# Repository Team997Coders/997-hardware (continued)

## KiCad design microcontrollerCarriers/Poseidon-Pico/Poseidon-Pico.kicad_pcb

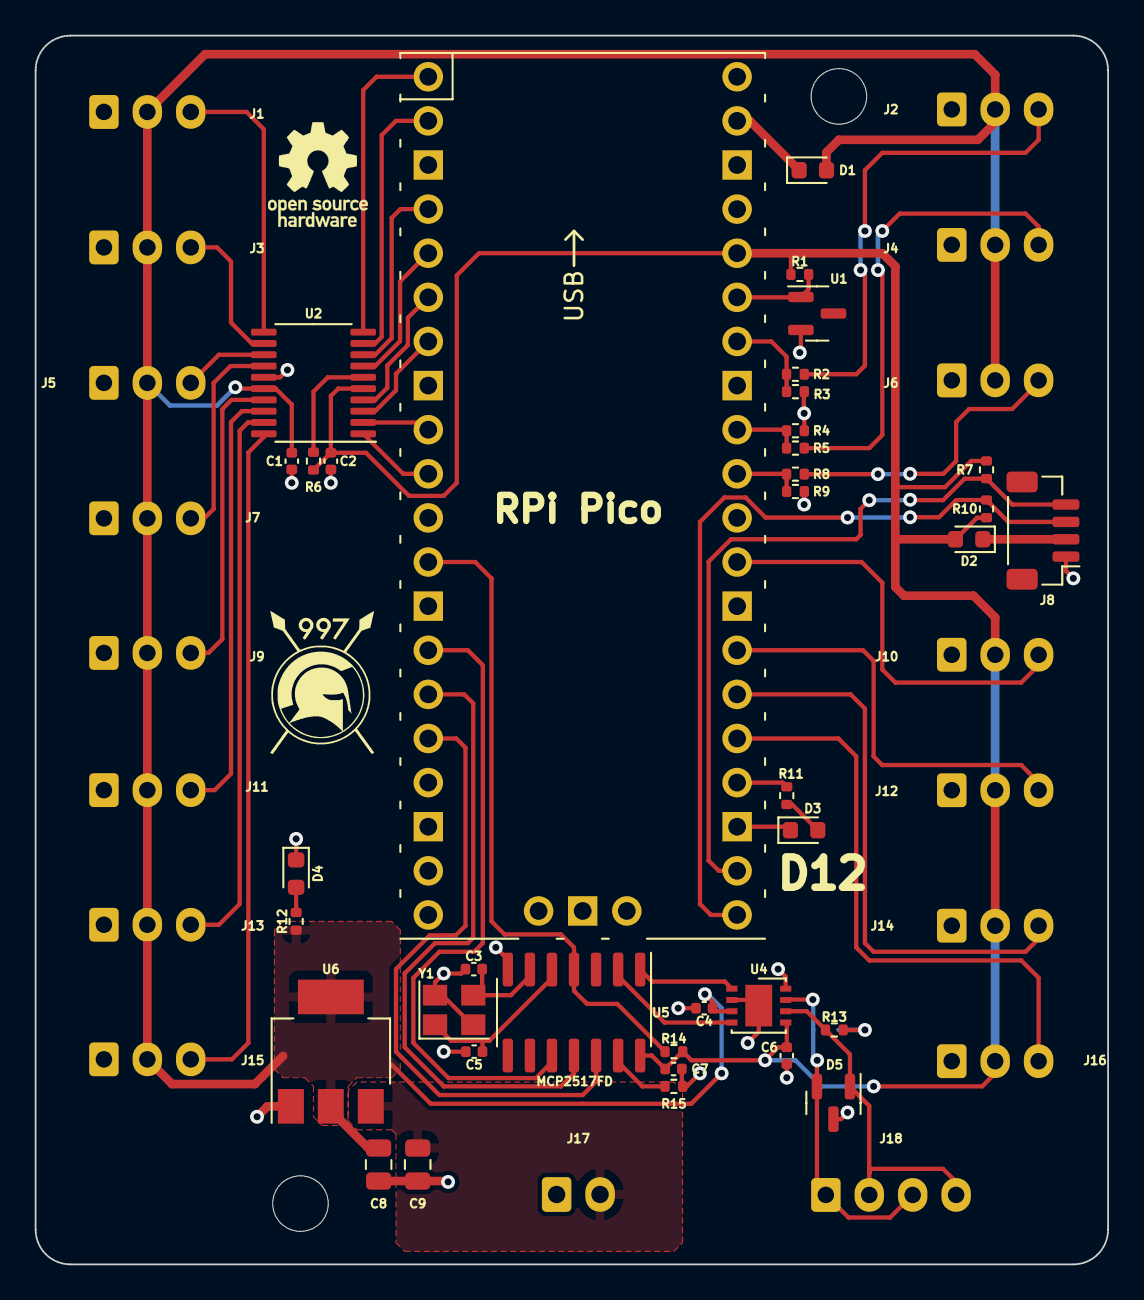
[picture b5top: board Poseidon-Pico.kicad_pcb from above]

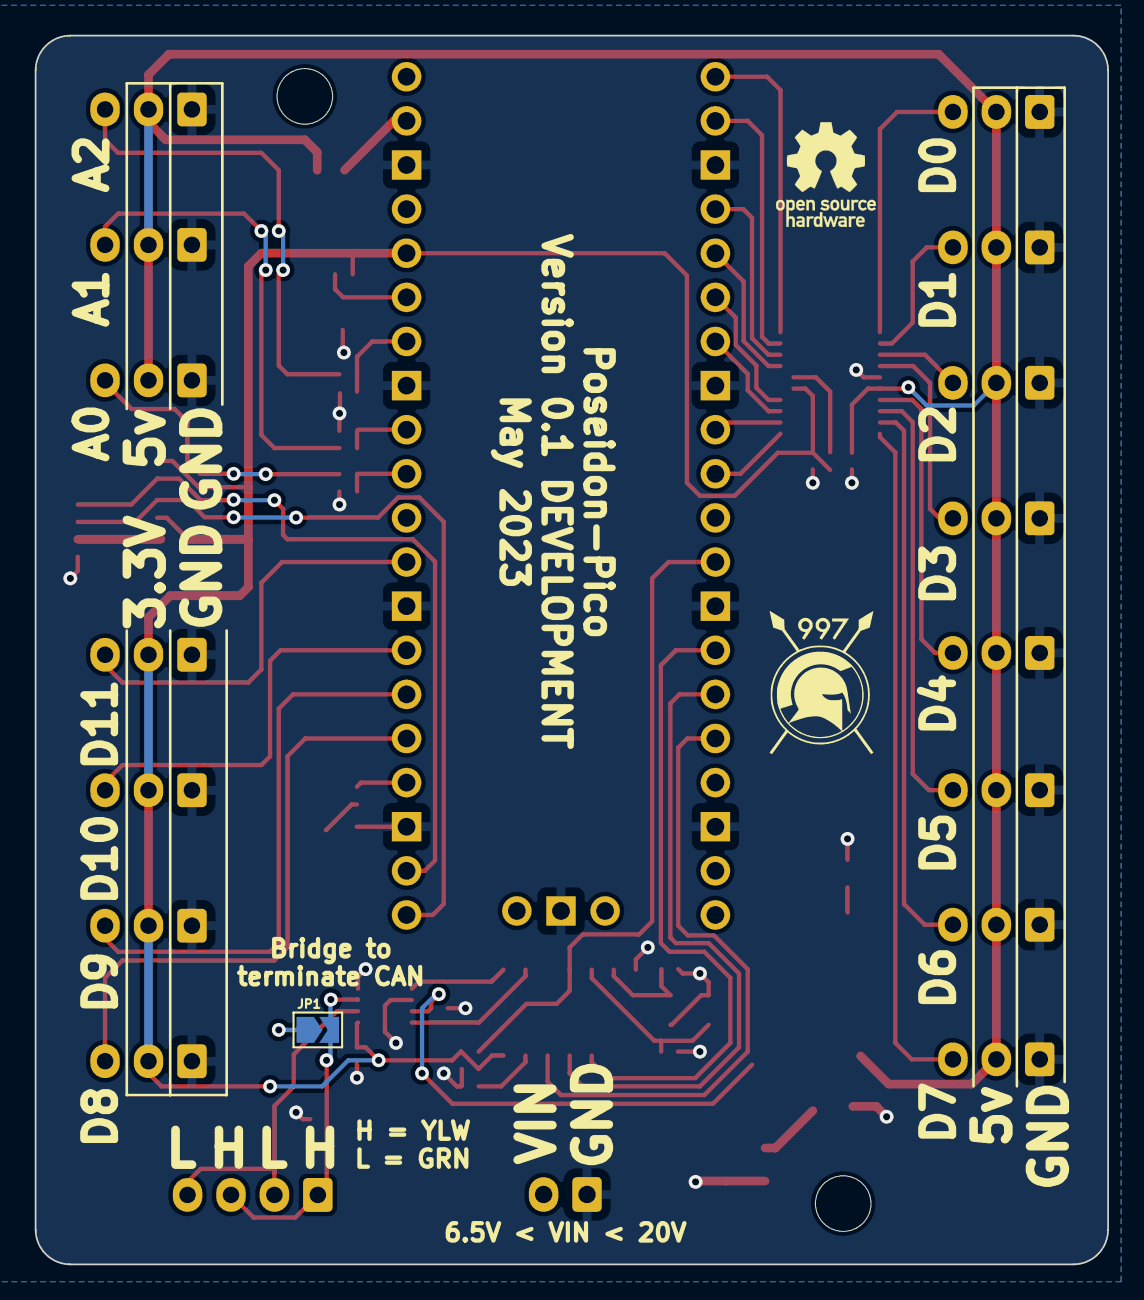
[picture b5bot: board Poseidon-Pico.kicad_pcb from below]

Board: 2 copper layers, 61.8 x 70.8 mm, 59 parts (3 on the bottom side), 51 nets.

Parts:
1, 2: LOGO; 997-big
C1, C2, C4, C6, C7: 0.1 uF; C_0402_1005Metric
C3, C5: 10 pF; C_0402_1005Metric
C8: 10 uF; C_0805_2012Metric
C9: 10 uF 35v; C_0805_2012Metric
D1, D2: D_Schottky; D_0603_1608Metric
D3, D4: LED; LED_0603_1608Metric
D5: NUP2105L; SOT-23
J1, J2, J3, J4, J5, J6, J7, J9, J10, J11, J12, J13, J14, J15, J16: Conn_01x03; JST_XH_B3B-XH-A_1x03_P2.50mm_Vertical
J8: Conn_01x04; JST_SH_BM04B-SRSS-TB_1x04-1MP_P1.00mm_Vertical
J17: Conn_01x02; JST_XH_B2B-XH-A_1x02_P2.50mm_Vertical
J18: Conn_01x04; JST_XH_B4B-XH-A_1x04_P2.50mm_Vertical
JP1: Jumper_2_Open; SolderJumper-2_P1.3mm_Open_TrianglePad1.0x1.5mm
R1, R6, R7, R10: 10k; R_0402_1005Metric
R2, R5, R8: 1.5k; R_0402_1005Metric
R3, R4, R9: 2.7k; R_0402_1005Metric
R11, R12: 300; R_0402_1005Metric
R13: 120; R_0402_1005Metric
R14, R15: 1k; R_0402_1005Metric
U1: LM4040DBZ-3; SOT-23
U2: TXB0108DQSR; TSSOP-20_4.4x6.5mm_P0.65mm
U3: Pico; RPi_Pico_SMD_TH
U4: MCP2542FDxMF; DFN-8-1EP_3x3mm_P0.65mm_EP1.55x2.4mm
U5: MCP2517FD-xSL; SOIC-14_3.9x8.7mm_P1.27mm
U6: NCP1117-5.0_SOT223; SOT-223-3_TabPin2
Y1: 40 MHz 9 pF; Crystal_SMD_3225-4Pin_3.2x2.5mm
oshw_b: OSHW-Logo_5.7x6mm_SilkScreen
oshw_f: OSHW-Logo_5.7x6mm_SilkScreen

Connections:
3ADC0: R8.2, R9.1, U3.31 (GPIO26_ADC0)
3ADC1: R4.1, R5.2, U3.32 (GPIO27_ADC1)
3ADC2: R2.2, R3.1, U3.34 (GPIO28_ADC2)
3GPIO0: U2.10 (A8), U3.1 (GPIO0)
3GPIO1: U2.9 (A7), U3.2 (GPIO1)
3GPIO2: U2.8 (A6), U3.4 (GPIO2)
3GPIO3: U2.7 (A5), U3.5 (GPIO3)
3GPIO4: U2.4 (A4), U3.6 (GPIO4)
3GPIO5: U2.3 (A3), U3.7 (GPIO5)
3GPIO6: U2.2 (A2), U3.9 (GPIO6)
3GPIO7: U2.1 (A1), U3.10 (GPIO7)
5ADC0: J6.3, R8.1
5ADC1: J4.3, R5.1
5ADC2: J2.3, R2.1
5GPIO0: J1.3, U2.11 (B8)
5GPIO1: J3.3, U2.12 (B7)
5GPIO2: J5.3, U2.13 (B6)
5GPIO3: J7.3, U2.14 (B5)
5GPIO4: J9.3, U2.17 (B4)
5GPIO5: J11.3, U2.18 (B3)
5GPIO6: J13.3, U2.19 (B2)
5GPIO7: J15.3, U2.20 (B1)
+3.3V: C2.1, C6.1, C7.1, D2.2 (A), J10.2, J12.2, J14.2, J16.2, R1.1, R6.1, R7.1, R10.1, R14.1, U2.5 (VCCA), U3.36 (3V3), U4.5 (VIO), U5.14 (VDD)
+5V: C1.1, C4.2, C8.1, D1.2 (A), J1.2, J2.2, J3.2, J4.2, J5.2, J6.2, J7.2, J9.2, J11.2, J13.2, J15.2, R12.2, U2.16 (VCCB), U4.3 (VDD), U6.2 (VO)
/CAN_CLK_A: C5.2, U5.5 (OSC2), Y1.1
/CAN_CLK_B: C3.1, U5.6 (OSC1), Y1.3
/RXCAN: U4.4 (RXD), U5.2 (RXCAN)
/TXCAN: U4.1 (TXD), U5.1 (TXCAN)
ADC_VREF: R1.2, U1.1 (K), U3.35 (ADC_VREF)
CANH: D5.2 (K), J18.1, J18.3, JP1.2 (B), U4.7 (CANH)
CANL: D5.1 (K), J18.2, J18.4, R13.2, U4.6 (CANL)
CAN_CS: R15.2, U5.13 (nCS)
CAN_INT: R14.2, U3.12 (GPIO9), U5.4 (~INT)
CAN_PICO: U3.15 (GPIO11), U5.11 (SDI)
CAN_POCI: U3.16 (GPIO12), U5.12 (SDO)
CAN_SCK: U3.14 (GPIO10), U5.10 (SCK)
GND: C1.2, C2.2, C3.2, C4.1, C5.1, C6.2, C7.2, C8.2, C9.2, D3.1 (K), D4.1 (K), D5.3 (A), J1.1, J2.1, J3.1, J4.1, J5.1, J6.1, J7.1, J8.1, J9.1, J10.1, J11.1, J12.1, J13.1, J14.1, J15.1, J16.1, J17.1, R3.2, R4.2, R9.2, R15.1, U1.2 (A), U2.15 (GND), U3.3 (GND), U3.8 (GND), U3.13 (GND), U3.18 (GND), U3.23 (GND), U3.28 (GND), U3.33 (AGND), U3.38 (GND), U3.42 (GND), U4.2 (VSS), U4.8 (STBY), U4.9 (VSS), U5.7 (VSS), U6.1 (GND), Y1.2, Y1.4
GPIO8: J16.3, U3.25 (GPIO19)
GPIO9: J14.3, U3.26 (GPIO20)
GPIO10: J12.3, U3.27 (GPIO21)
GPIO11: J10.3, U3.29 (GPIO22)
unnamed: D1.1 (K), U3.39 (VSYS)
unnamed: D2.1 (K), J8.2
unnamed: D3.2 (A), R11.1
unnamed: D4.2 (A), R12.1
unnamed: JP1.1 (A), R13.1
unnamed: R6.2, U2.6 (OE)
unnamed: R11.2, U3.24 (GPIO18)
SCL: J8.4, R7.2, U3.22 (GPIO17)
SDA: J8.3, R10.2, U3.21 (GPIO16)
VIN: C9.1, J17.2, U6.3 (VI)

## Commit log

2023-07-26 Initial commit, w/ data port adapter
2023-07-26 Git add zipped gerbers in hook script
2023-07-26 Source files for microcontroller carrier projects
2023-07-26 Add power distribution board
2023-08-05 Fix JST-SH 3d model and pins, add silkscreen to Pico
2023-08-11 Downgrade CAN controller to 2.0B for driver compatibility
2023-08-12 Switch to F042 w/ internal CAN controller, change stackup
2023-08-12 Tweak via + some silkscreen to pass DRC
2023-08-12 Add solder jumpers to switch between modes
2023-08-12 Fixed overzealous image generation
2023-08-16 Add second bulk cap
